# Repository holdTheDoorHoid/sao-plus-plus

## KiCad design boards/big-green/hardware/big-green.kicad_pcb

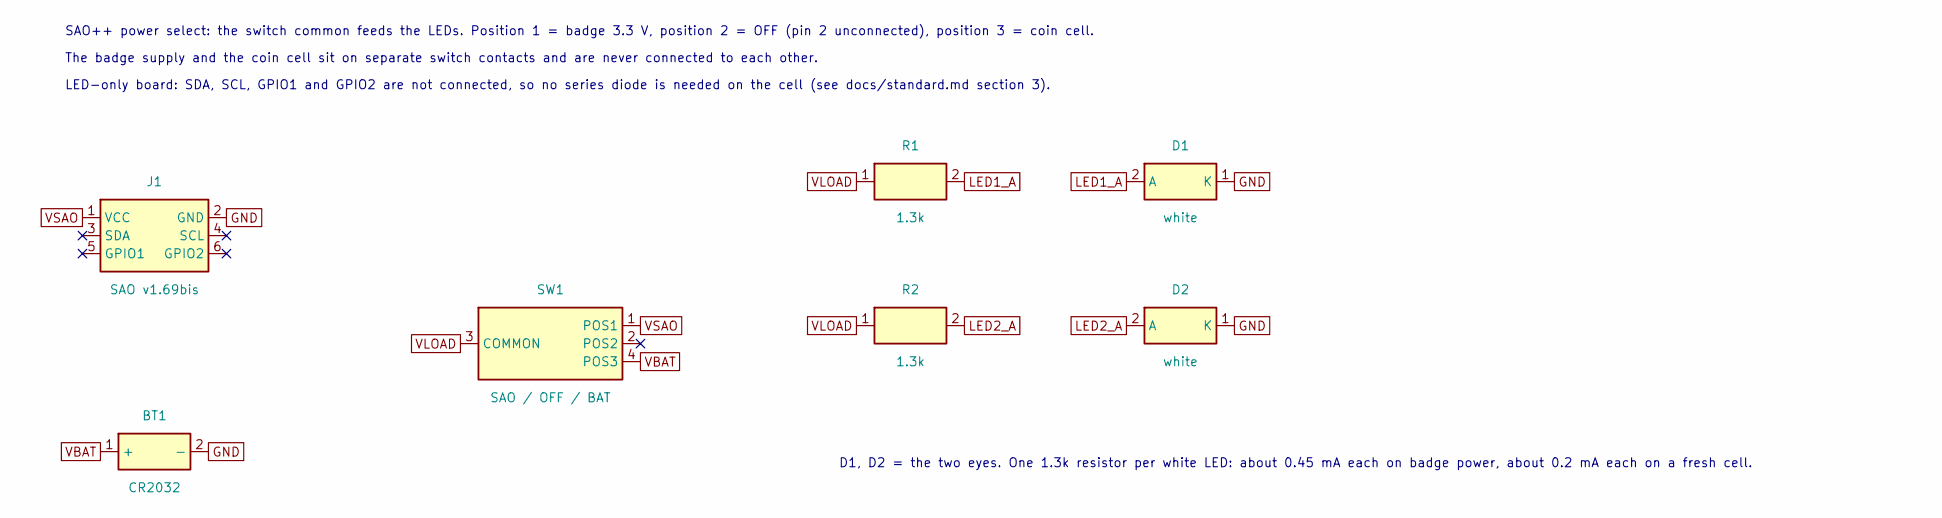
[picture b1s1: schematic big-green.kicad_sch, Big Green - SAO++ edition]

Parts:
BT1: CR2032; SAOPP_BAT-01_CR2032_SMD_TE_BAT-HLD-001; MPN BAT-HLD-001; LCSC C7501066
D1, D2: white; SAOPP_LED-10_1206_ReverseMount_ThroughBoard; MPN LTW-C230DS; LCSC C575513
J1: SAO v1.69bis; SAOPP_CONN-01_BoxHeader_2x03_P2.54mm_SMD_XFCN_BH254VS-6P; MPN BH254VS-6P; LCSC C492445
R1, R2: 1.3k; SAOPP_R_0603_1608Metric; MPN 0603WAF1301T5E; LCSC C22767
SW1: SAO / OFF / BAT; SAOPP_SW-01_Slide_SP3T_CK_PCM13SMTR; MPN PCM13SMTR; LCSC C221842

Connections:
GND: BT1.2 (-), D1.1 (K), D2.1 (K), J1.2 (GND)
LED1_A: D1.2 (A), R1.2
LED2_A: D2.2 (A), R2.2
VBAT: BT1.1 (+), SW1.4 (POS3)
VLOAD: R1.1, R2.1, SW1.3 (COMMON)
VSAO: J1.1 (VCC), SW1.1 (POS1)

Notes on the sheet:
SAO++ power select: the switch common feeds the LEDs. Position 1 = badge 3.3 V, position 2 = OFF (pin 2 unconnected), position 3 = coin cell.
The badge supply and the coin cell sit on separate switch contacts and are never connected to each other.
LED-only board: SDA, SCL, GPIO1 and GPIO2 are not connected, so no series diode is needed on the cell (see docs/standard.md section 3).
D1, D2 = the two eyes. One 1.3k resistor per white LED: about 0.45 mA each on badge power, about 0.2 mA each on a fresh cell.

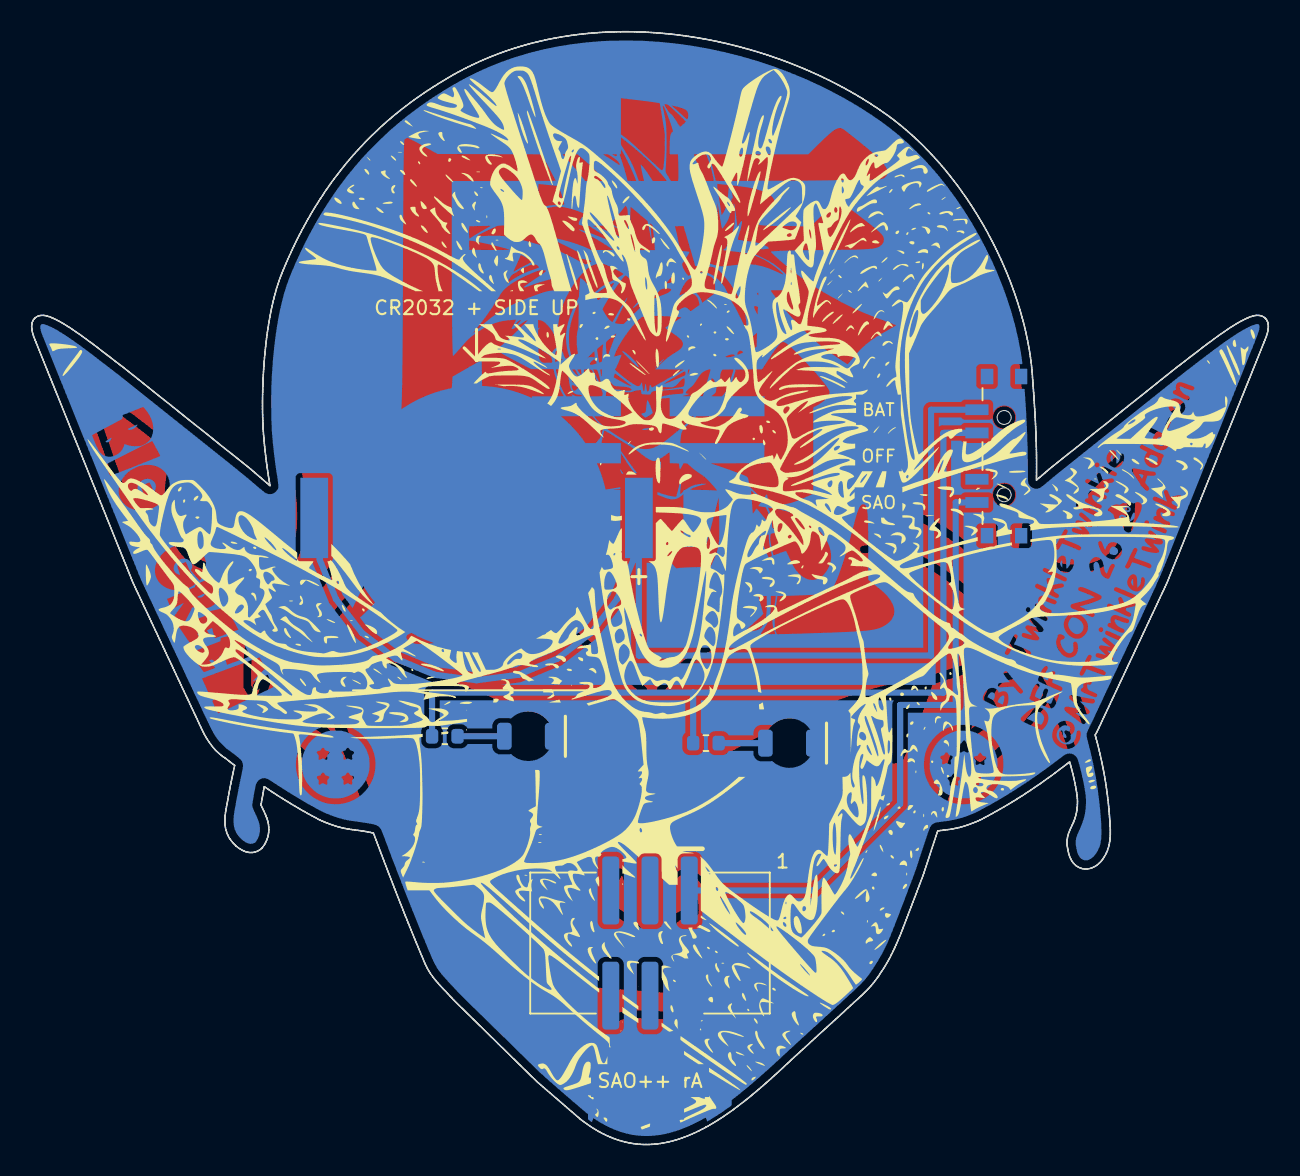
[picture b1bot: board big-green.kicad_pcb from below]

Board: 2 copper layers, 80.0 x 72.0 mm, 12 parts (7 on the bottom side), 6 nets.

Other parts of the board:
B.Cu: LOGO; B.Cu_g1620
B.Silk: LOGO; B.Silk_g1624
F.Cu: LOGO; F.Cu_g1626
F.Mask: LOGO; F.Mask_g1628
F.Silk: LOGO; F.Silk_g1630

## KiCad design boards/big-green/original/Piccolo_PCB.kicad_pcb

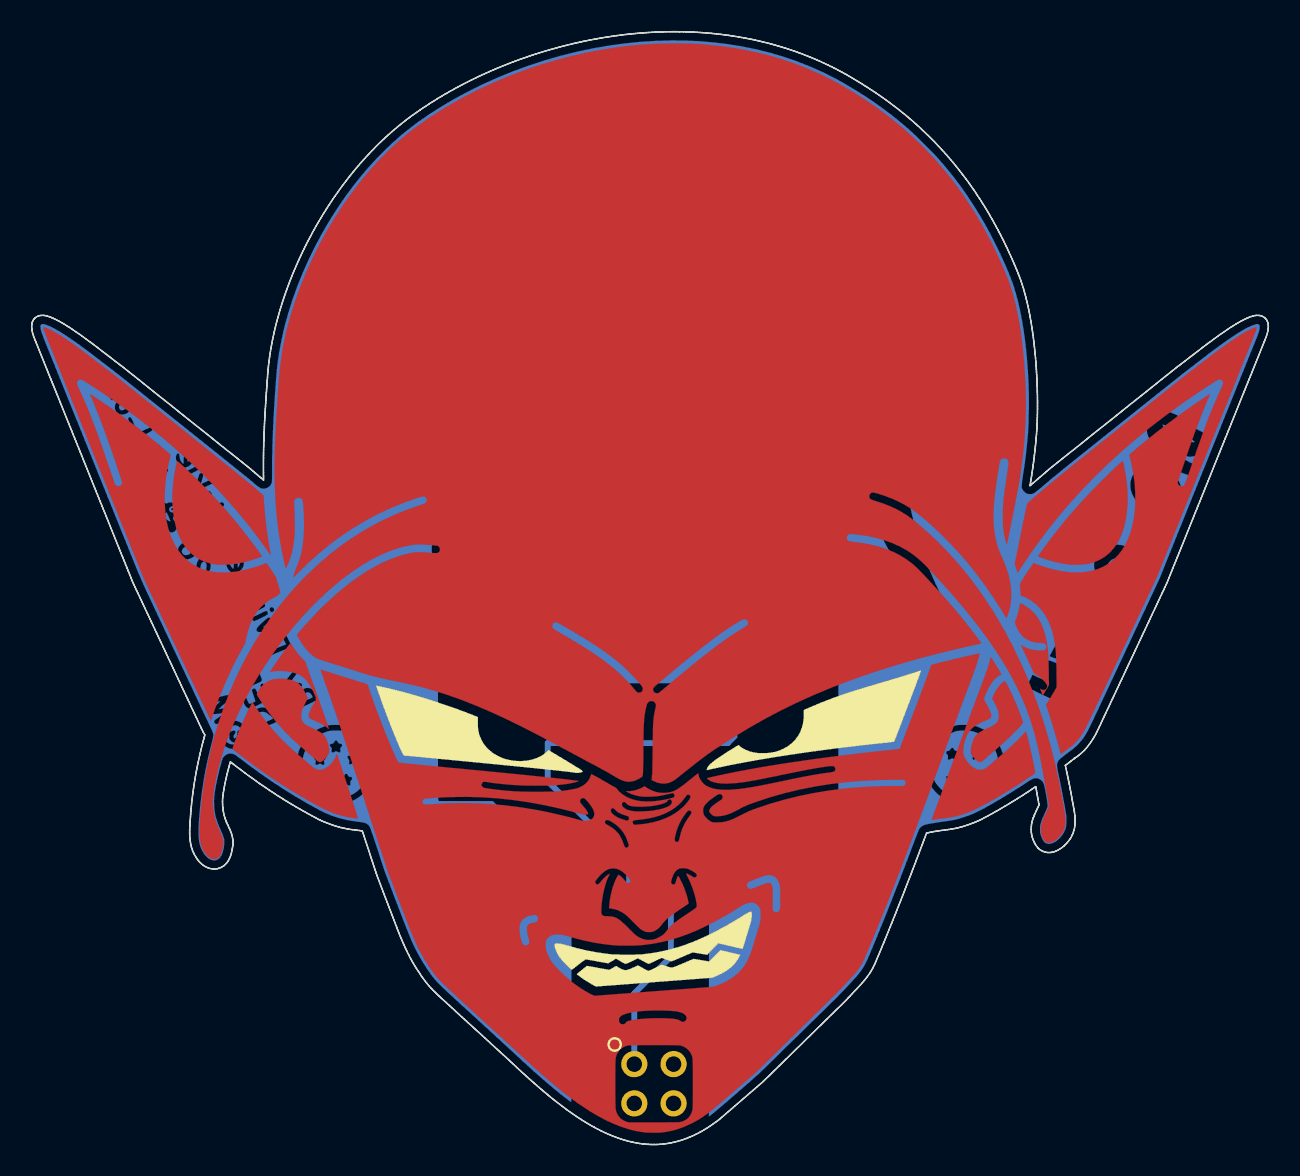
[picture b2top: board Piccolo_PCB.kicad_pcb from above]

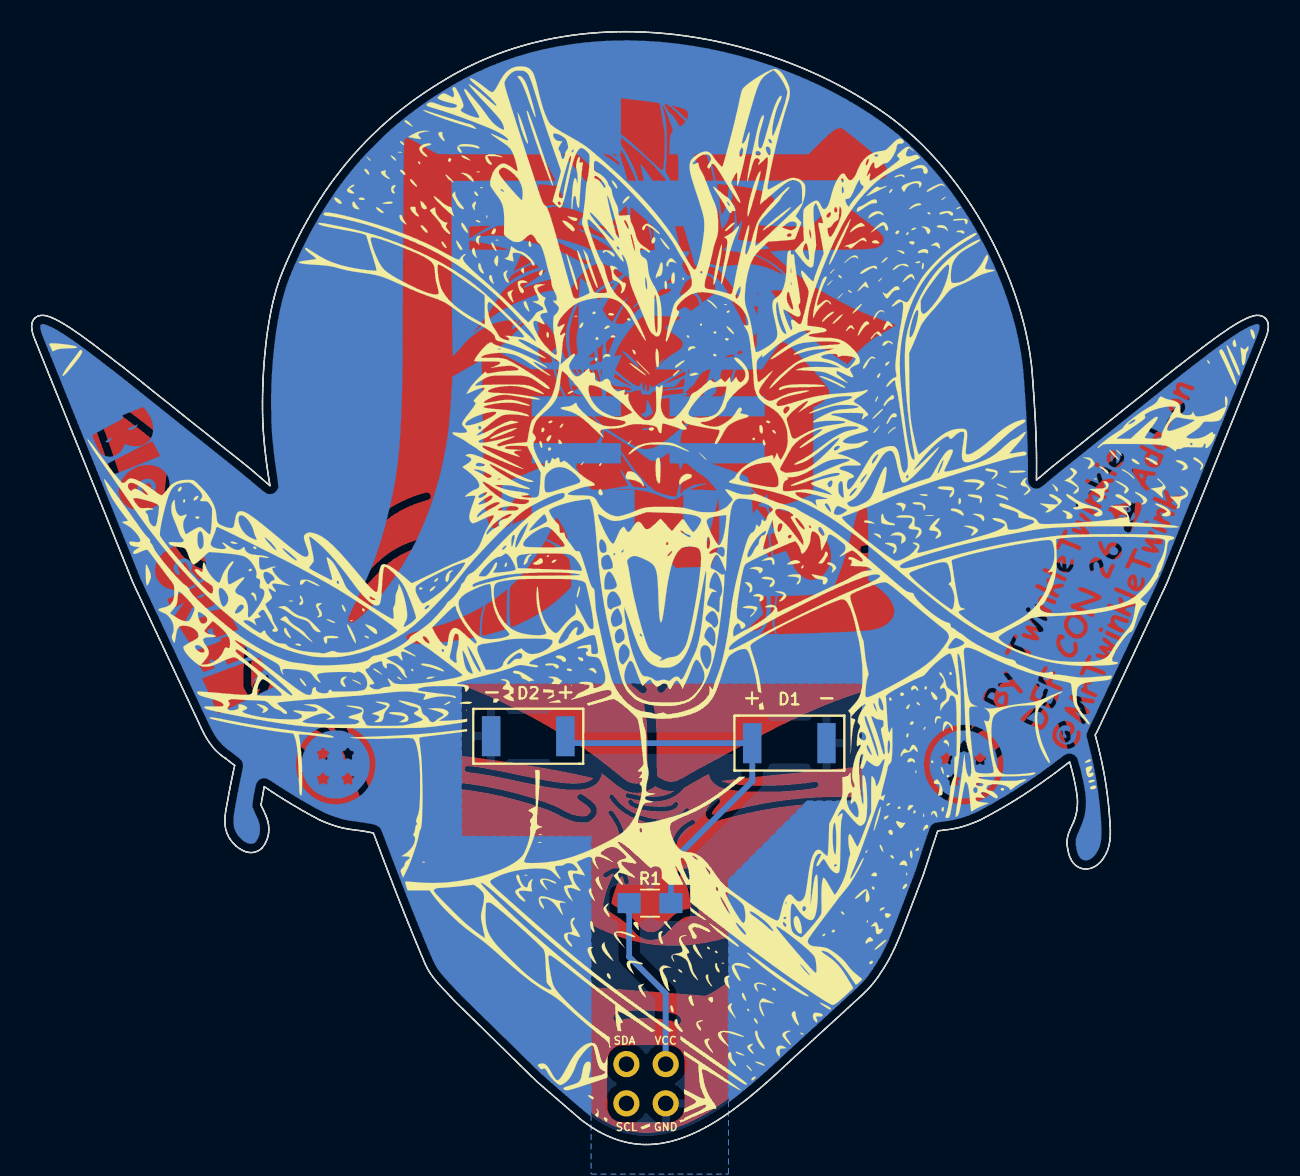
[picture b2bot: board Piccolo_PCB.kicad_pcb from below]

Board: 2 copper layers, 80.0 x 72.0 mm, 9 parts (3 on the bottom side), 3 nets.

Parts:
B.Cu: LOGO; B.Cu_g1620
B.Silk: LOGO; B.Silk_g1624
D1, D2: LED; LED_OSRAM_TOPLED_LxT776
F.Cu: LOGO; F.Cu_g1626
F.Mask: LOGO; F.Mask_g1628
F.Silk: LOGO; F.Silk_g1630
R1: R51; R_0805_HandSoldering
X1: Badgelife_shitty_connector; Badgelife-Shitty-2x2

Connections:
unnamed: D1.1, D2.1, X1.2
unnamed: D1.2, D2.2, R1.1
unnamed: R1.2, X1.1

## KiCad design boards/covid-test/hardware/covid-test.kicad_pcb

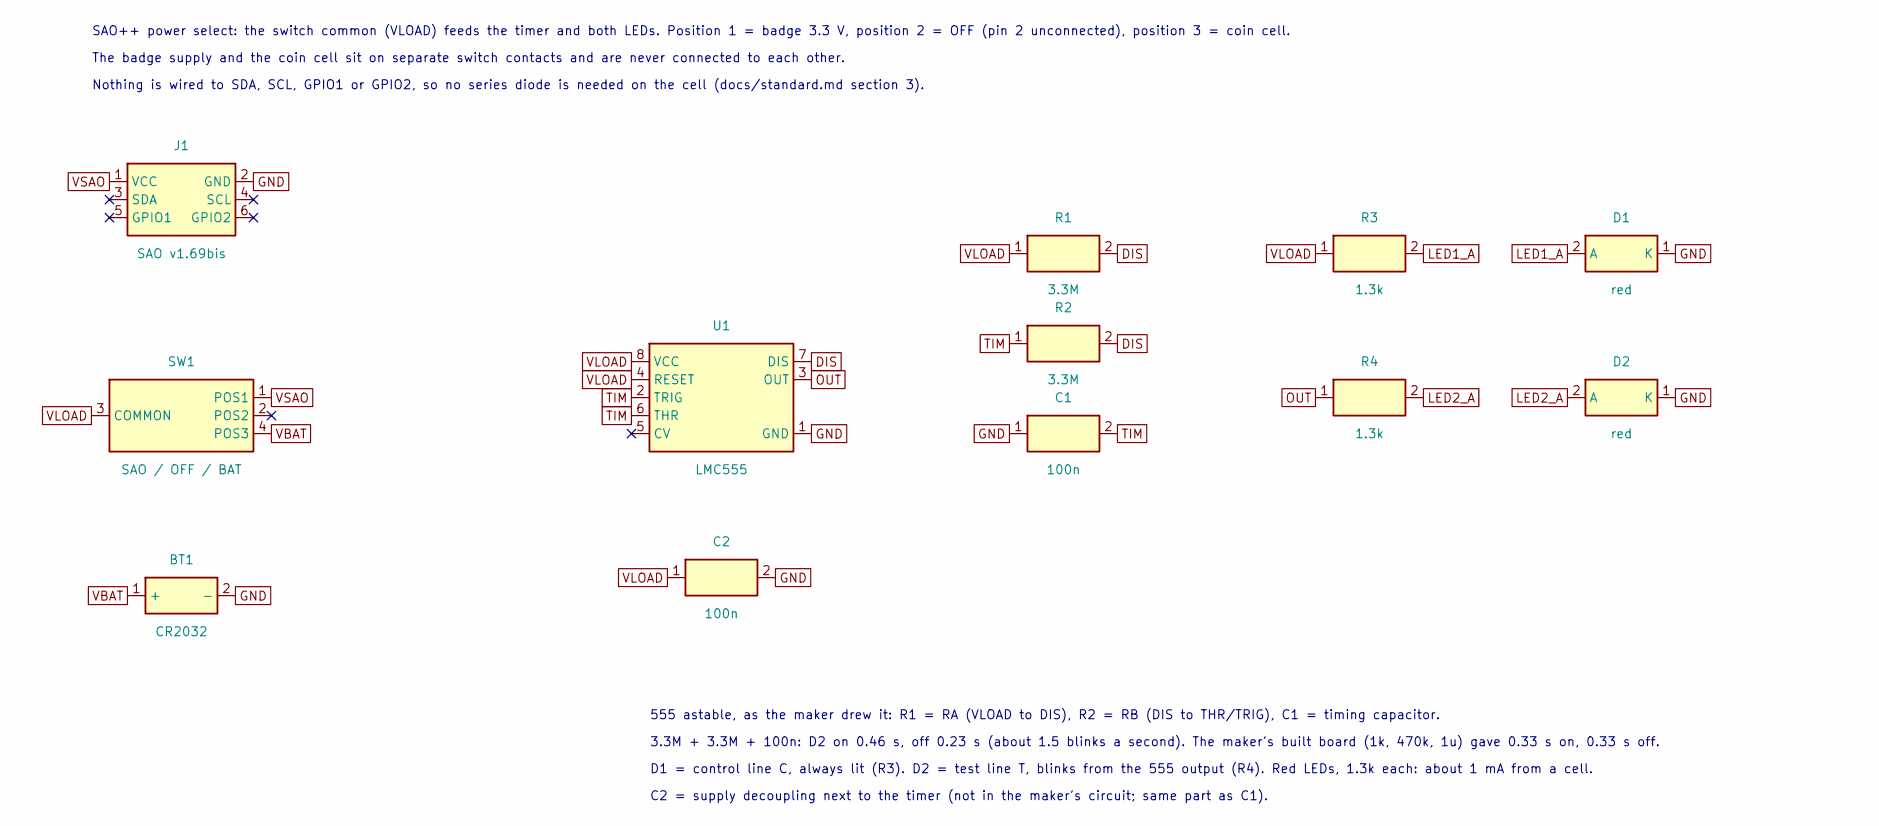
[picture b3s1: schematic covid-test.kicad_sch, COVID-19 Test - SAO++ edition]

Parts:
BT1: CR2032; SAOPP_BAT-01_CR2032_SMD_TE_BAT-HLD-001; MPN BAT-HLD-001; LCSC C7501066
C1, C2: 100n; SAOPP_C_0603_1608Metric; MPN CC0603KRX7R9BB104; LCSC C14663
D1, D2: red; SAOPP_LED-10_1206_ReverseMount_ThroughBoard; MPN LTST-C230KRKT; LCSC C125107
J1: SAO v1.69bis; SAOPP_CONN-01_BoxHeader_2x03_P2.54mm_SMD_XFCN_BH254VS-6P; MPN BH254VS-6P; LCSC C492445
R1, R2: 3.3M; R_0603_1608Metric; MPN 0603WAF3304T5E; LCSC C26096
R3, R4: 1.3k; SAOPP_R_0603_1608Metric; MPN 0603WAF1301T5E; LCSC C22767
SW1: SAO / OFF / BAT; SAOPP_SW-01_Slide_SP3T_CK_PCM13SMTR; MPN PCM13SMTR; LCSC C221842
U1: LMC555; SOIC-8_3.9x4.9mm_P1.27mm; MPN LMC555CMX/NOPB; LCSC C90760

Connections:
DIS: R1.2, R2.2, U1.7 (DIS)
GND: BT1.2 (-), C1.1, C2.2, D1.1 (K), D2.1 (K), J1.2 (GND), U1.1 (GND)
LED1_A: D1.2 (A), R3.2
LED2_A: D2.2 (A), R4.2
OUT: R4.1, U1.3 (OUT)
TIM: C1.2, R2.1, U1.2 (TRIG), U1.6 (THR)
VBAT: BT1.1 (+), SW1.4 (POS3)
VLOAD: C2.1, R1.1, R3.1, SW1.3 (COMMON), U1.4 (RESET), U1.8 (VCC)
VSAO: J1.1 (VCC), SW1.1 (POS1)

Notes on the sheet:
SAO++ power select: the switch common (VLOAD) feeds the timer and both LEDs. Position 1 = badge 3.3 V, position 2 = OFF (pin 2 unconnected), position 3 = coin cell.
The badge supply and the coin cell sit on separate switch contacts and are never connected to each other.
Nothing is wired to SDA, SCL, GPIO1 or GPIO2, so no series diode is needed on the cell (docs/standard.md section 3).
555 astable, as the maker drew it: R1 = RA (VLOAD to DIS), R2 = RB (DIS to THR/TRIG), C1 = timing capacitor.
3.3M + 3.3M + 100n: D2 on 0.46 s, off 0.23 s (about 1.5 blinks a second). The maker's built board (1k, 470k, 1u) gave 0.33 s on, 0.33 s off.
D1 = control line C, always lit (R3). D2 = test line T, blinks from the 555 output (R4). Red LEDs, 1.3k each: about 1 mA from a cell.
C2 = supply decoupling next to the timer (not in the maker's circuit; same part as C1).

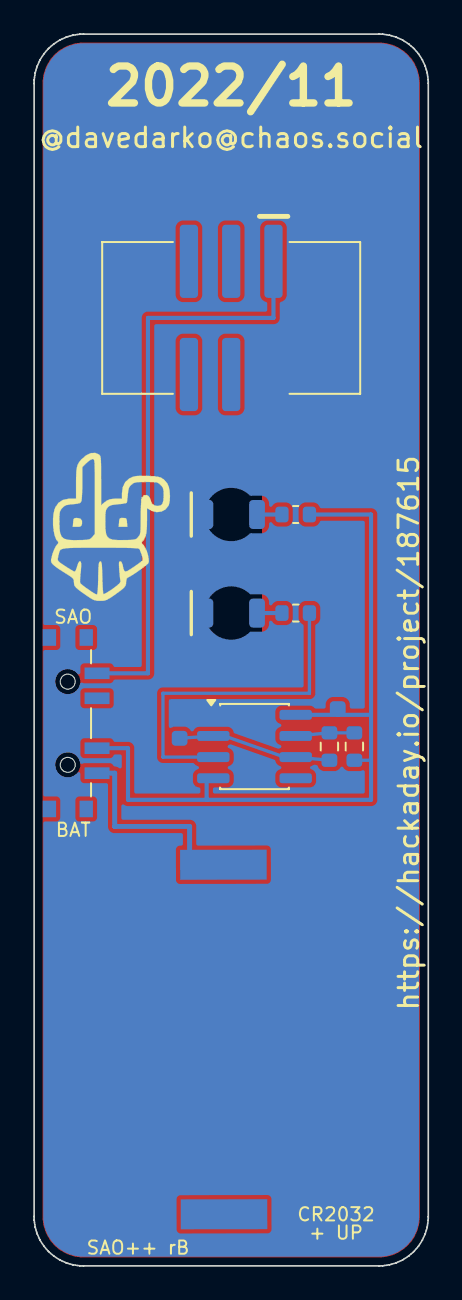
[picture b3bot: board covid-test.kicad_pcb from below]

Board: 2 copper layers, 23.7 x 74.0 mm, 14 parts (13 on the bottom side), 9 nets.

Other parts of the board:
Ref**: Val**; finalShadow
Ref**#2: Val**; davedarko_logo_silk_ext

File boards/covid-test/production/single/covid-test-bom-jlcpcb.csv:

Comment,Designator,Footprint,LCSC Part #
CR2032,BT1,SAOPP_BAT-01_CR2032_SMD_TE_BAT-HLD-001,C7501066
100n,"C1,C2",SAOPP_C_0603_1608Metric,C14663
red,"D1,D2",SAOPP_LED-10_1206_ReverseMount_ThroughBoard,C125107
SAO v1.69bis,J1,SAOPP_CONN-01_BoxHeader_2x03_P2.54mm_SMD_XFCN_BH254VS-6P,C492445
3.3M,"R1,R2",R_0603_1608Metric,C26096
1.3k,"R3,R4",SAOPP_R_0603_1608Metric,C22767
SAO / OFF / BAT,SW1,SAOPP_SW-01_Slide_SP3T_CK_PCM13SMTR,C221842
LMC555,U1,SOIC-8_3.9x4.9mm_P1.27mm,C90760

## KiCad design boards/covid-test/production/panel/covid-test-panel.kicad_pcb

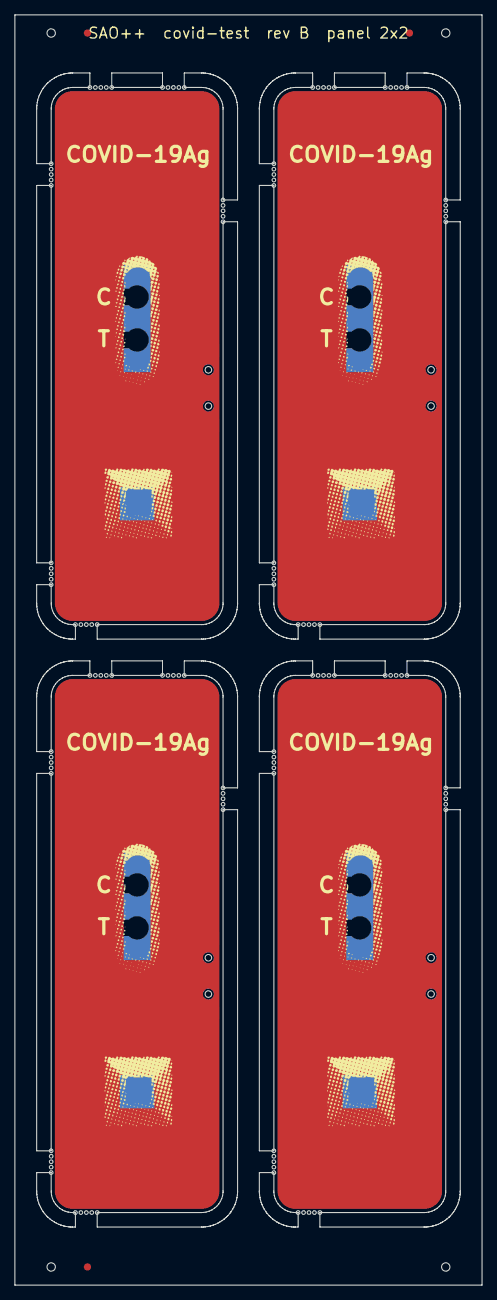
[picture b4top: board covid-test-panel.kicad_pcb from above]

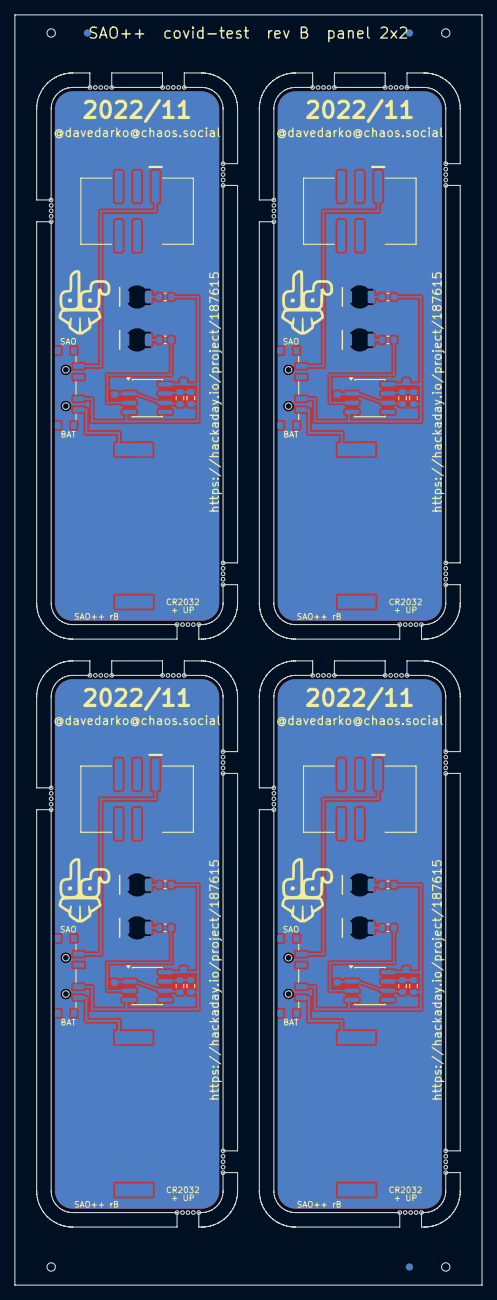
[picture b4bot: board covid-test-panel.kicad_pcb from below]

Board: 2 copper layers, 64.4 x 175.0 mm, 56 parts (52 on the bottom side), 36 nets.

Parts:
BT101, BT201, BT301, BT401: CR2032; SAOPP_BAT-01_CR2032_SMD_TE_BAT-HLD-001
C101, C102, C201, C202, C301, C302, C401, C402: 100n; SAOPP_C_0603_1608Metric
D101, D102, D201, D202, D301, D302, D401, D402: red; SAOPP_LED-10_1206_ReverseMount_ThroughBoard
J101, J201, J301, J401: SAO v1.69bis; SAOPP_CONN-01_BoxHeader_2x03_P2.54mm_SMD_XFCN_BH254VS-6P
R101, R102, R201, R202, R301, R302, R401, R402: 3.3M; R_0603_1608Metric
R103, R104, R203, R204, R303, R304, R403, R404: 1.3k; SAOPP_R_0603_1608Metric
Ref**: Val**; finalShadow
Ref**#2, Ref**#3, Ref**#4: Val**; finalShadow
Ref**#5, Ref**#6, Ref**#7, Ref**#8: Val**; davedarko_logo_silk_ext
SW101, SW201, SW301, SW401: SAO / OFF / BAT; SAOPP_SW-01_Slide_SP3T_CK_PCM13SMTR
U101, U201, U301, U401: LMC555; SOIC-8_3.9x4.9mm_P1.27mm

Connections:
B2-DIS: R201.2, R202.2, U201.7
B2-GND: BT201.2, C201.1, C202.2, D201.1, D202.1, J201.2, U201.1
B2-LED1_A: D201.2, R203.2
B2-LED2_A: D202.2, R204.2
B2-OUT: R204.1, U201.3
B2-TIM: C201.2, R202.1, U201.2, U201.6
B2-VBAT: BT201.1, SW201.4
B2-VLOAD: C202.1, R201.1, R203.1, SW201.3, U201.4, U201.8
B2-VSAO: J201.1, SW201.1
B3-DIS: R301.2, R302.2, U301.7
B3-GND: BT301.2, C301.1, C302.2, D301.1, D302.1, J301.2, U301.1
B3-LED1_A: D301.2, R303.2
B3-LED2_A: D302.2, R304.2
B3-OUT: R304.1, U301.3
B3-TIM: C301.2, R302.1, U301.2, U301.6
B3-VBAT: BT301.1, SW301.4
B3-VLOAD: C302.1, R301.1, R303.1, SW301.3, U301.4, U301.8
B3-VSAO: J301.1, SW301.1
B4-DIS: R401.2, R402.2, U401.7
B4-GND: BT401.2, C401.1, C402.2, D401.1, D402.1, J401.2, U401.1
B4-LED1_A: D401.2, R403.2
B4-LED2_A: D402.2, R404.2
B4-OUT: R404.1, U401.3
B4-TIM: C401.2, R402.1, U401.2, U401.6
B4-VBAT: BT401.1, SW401.4
B4-VLOAD: C402.1, R401.1, R403.1, SW401.3, U401.4, U401.8
B4-VSAO: J401.1, SW401.1
DIS: R101.2, R102.2, U101.7
GND: BT101.2, C101.1, C102.2, D101.1, D102.1, J101.2, U101.1
LED1_A: D101.2, R103.2
LED2_A: D102.2, R104.2
OUT: R104.1, U101.3
TIM: C101.2, R102.1, U101.2, U101.6
VBAT: BT101.1, SW101.4
VLOAD: C102.1, R101.1, R103.1, SW101.3, U101.4, U101.8
VSAO: J101.1, SW101.1

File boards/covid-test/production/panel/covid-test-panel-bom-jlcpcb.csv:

Comment,Designator,Footprint,LCSC Part #
CR2032,"BT101,BT201,BT301,BT401",SAOPP_BAT-01_CR2032_SMD_TE_BAT-HLD-001,C7501066
100n,"C101,C102,C201,C202,C301,C302,C401,C402",SAOPP_C_0603_1608Metric,C14663
red,"D101,D102,D201,D202,D301,D302,D401,D402",SAOPP_LED-10_1206_ReverseMount_ThroughBoard,C125107
SAO v1.69bis,"J101,J201,J301,J401",SAOPP_CONN-01_BoxHeader_2x03_P2.54mm_SMD_XFCN_BH254VS-6P,C492445
3.3M,"R101,R102,R201,R202,R301,R302,R401,R402",R_0603_1608Metric,C26096
1.3k,"R103,R104,R203,R204,R303,R304,R403,R404",SAOPP_R_0603_1608Metric,C22767
SAO / OFF / BAT,"SW101,SW201,SW301,SW401",SAOPP_SW-01_Slide_SP3T_CK_PCM13SMTR,C221842
LMC555,"U101,U201,U301,U401",SOIC-8_3.9x4.9mm_P1.27mm,C90760

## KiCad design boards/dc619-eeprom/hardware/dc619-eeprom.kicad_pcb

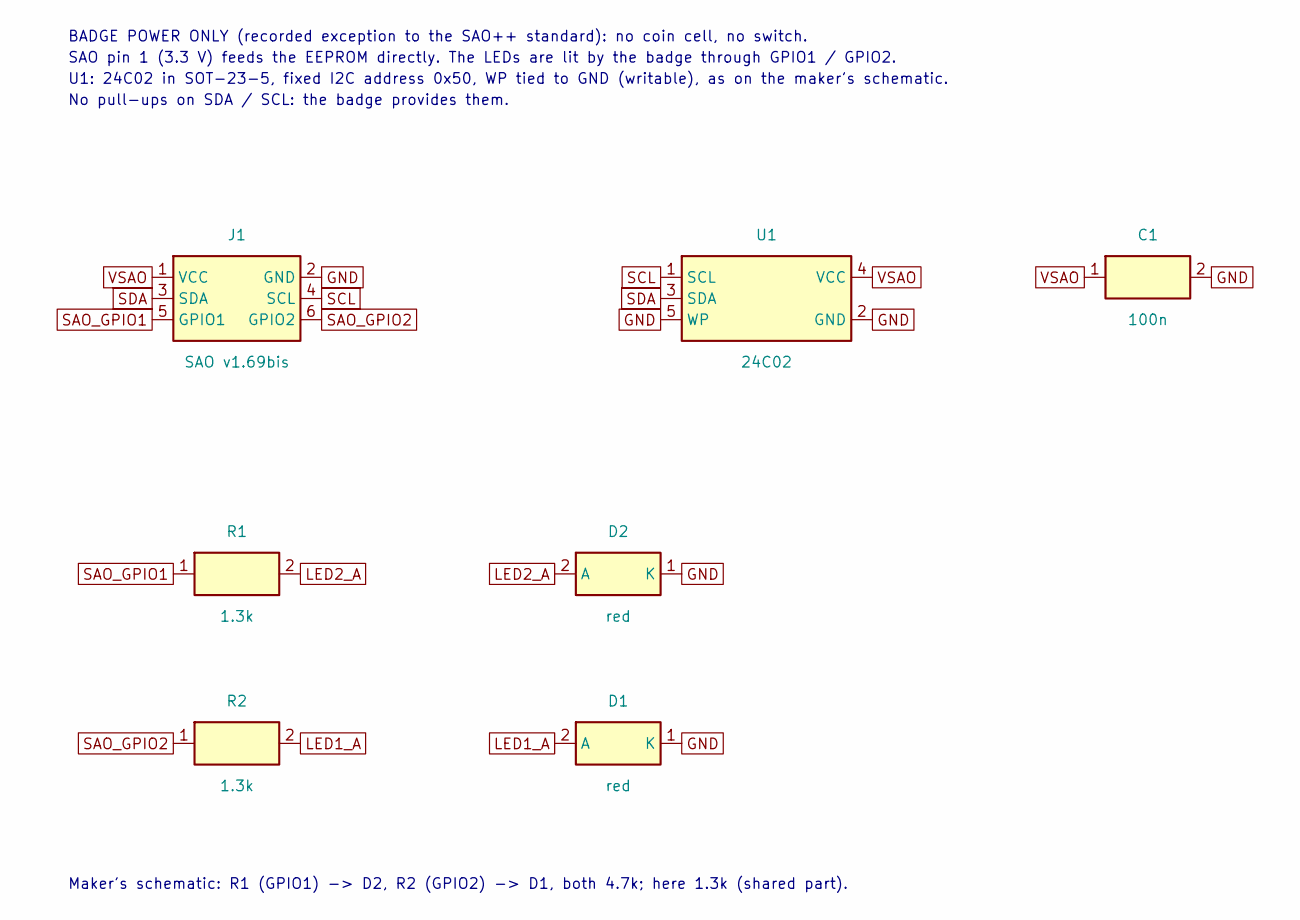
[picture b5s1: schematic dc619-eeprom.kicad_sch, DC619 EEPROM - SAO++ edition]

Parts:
C1: 100n; SAOPP_C_0603_1608Metric; MPN CC0603KRX7R9BB104; LCSC C14663
D1, D2: red; SAOPP_LED-10_1206_ReverseMount_ThroughBoard; MPN LTST-C230KRKT; LCSC C125107
J1: SAO v1.69bis; SAOPP_CONN-01_BoxHeader_2x03_P2.54mm_SMD_XFCN_BH254VS-6P; MPN BH254VS-6P; LCSC C492445
R1, R2: 1.3k; SAOPP_R_0603_1608Metric; MPN 0603WAF1301T5E; LCSC C22767
U1: 24C02; SOT-23-5; MPN AD24C02; LCSC C5125083

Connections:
GND: C1.2, D1.1 (K), D2.1 (K), J1.2 (GND), U1.2 (GND), U1.5 (WP)
LED1_A: D1.2 (A), R2.2
LED2_A: D2.2 (A), R1.2
SAO_GPIO1: J1.5 (GPIO1), R1.1
SAO_GPIO2: J1.6 (GPIO2), R2.1
SCL: J1.4 (SCL), U1.1 (SCL)
SDA: J1.3 (SDA), U1.3 (SDA)
VSAO: C1.1, J1.1 (VCC), U1.4 (VCC)

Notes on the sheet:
BADGE POWER ONLY (recorded exception to the SAO++ standard): no coin cell, no switch.
SAO pin 1 (3.3 V) feeds the EEPROM directly. The LEDs are lit by the badge through GPIO1 / GPIO2.
U1: 24C02 in SOT-23-5, fixed I2C address 0x50, WP tied to GND (writable), as on the maker's schematic.
No pull-ups on SDA / SCL: the badge provides them.
Maker's schematic: R1 (GPIO1) -> D2, R2 (GPIO2) -> D1, both 4.7k; here 1.3k (shared part).

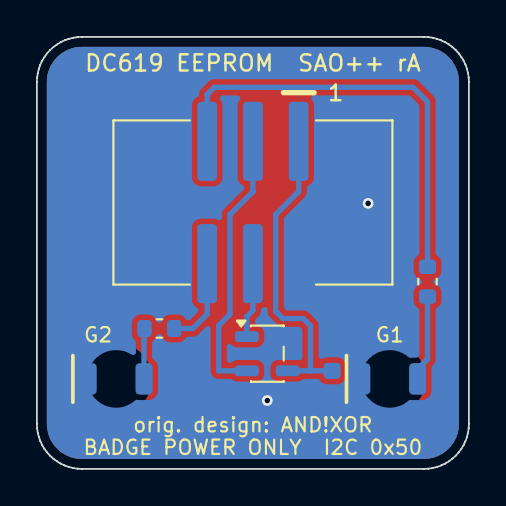
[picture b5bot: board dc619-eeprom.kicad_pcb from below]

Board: 2 copper layers, 24.0 x 24.0 mm, 7 parts (7 on the bottom side), 8 nets.

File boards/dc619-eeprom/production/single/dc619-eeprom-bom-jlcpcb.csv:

Comment,Designator,Footprint,LCSC Part #
100n,C1,SAOPP_C_0603_1608Metric,C14663
red,"D1,D2",SAOPP_LED-10_1206_ReverseMount_ThroughBoard,C125107
SAO v1.69bis,J1,SAOPP_CONN-01_BoxHeader_2x03_P2.54mm_SMD_XFCN_BH254VS-6P,C492445
1.3k,"R1,R2",SAOPP_R_0603_1608Metric,C22767
24C02,U1,SOT-23-5,C5125083

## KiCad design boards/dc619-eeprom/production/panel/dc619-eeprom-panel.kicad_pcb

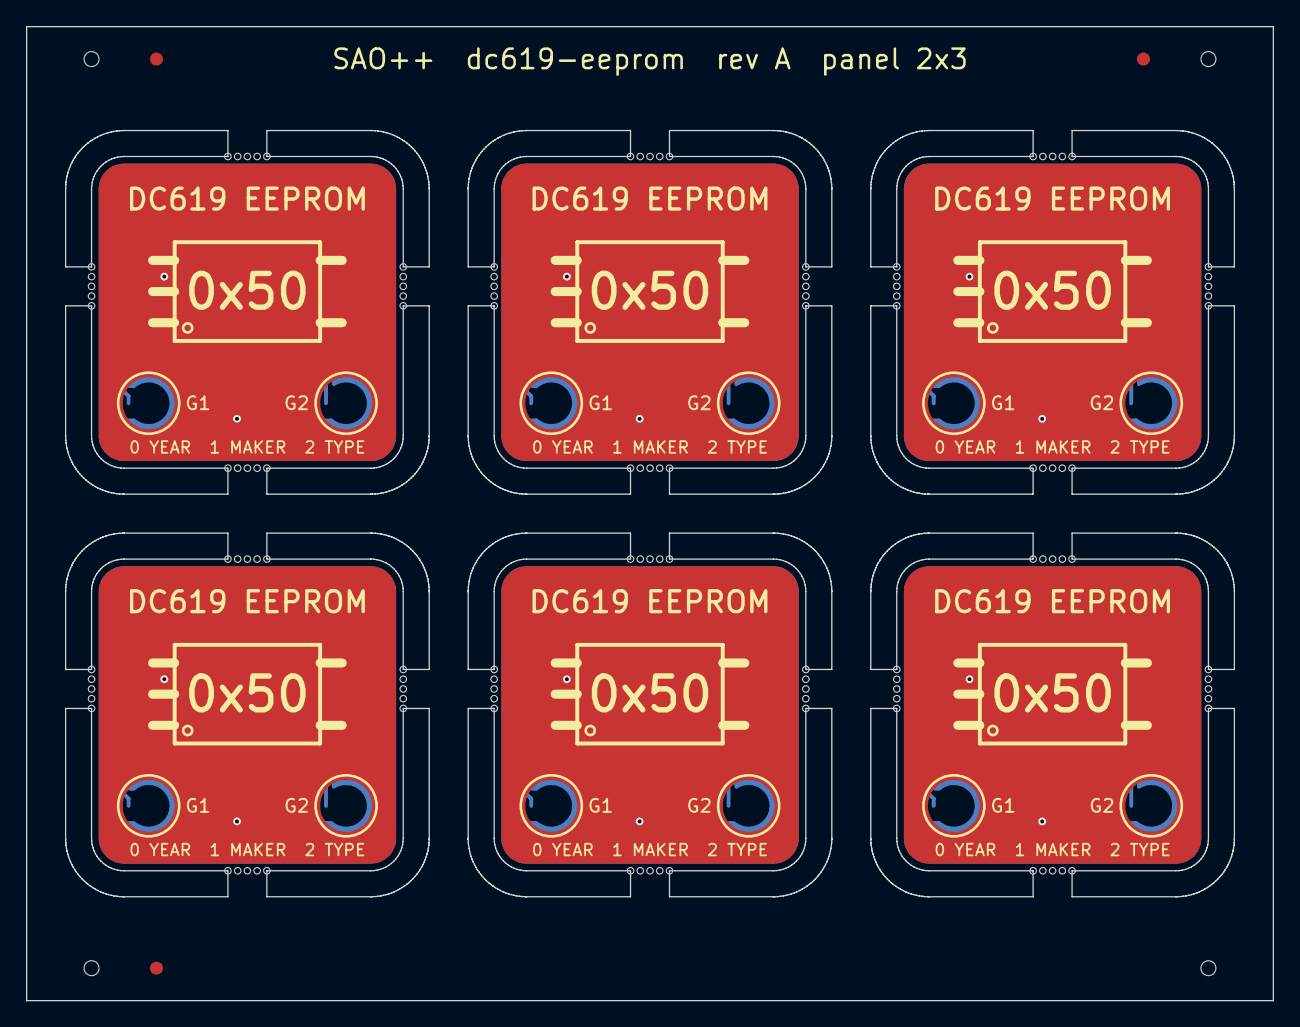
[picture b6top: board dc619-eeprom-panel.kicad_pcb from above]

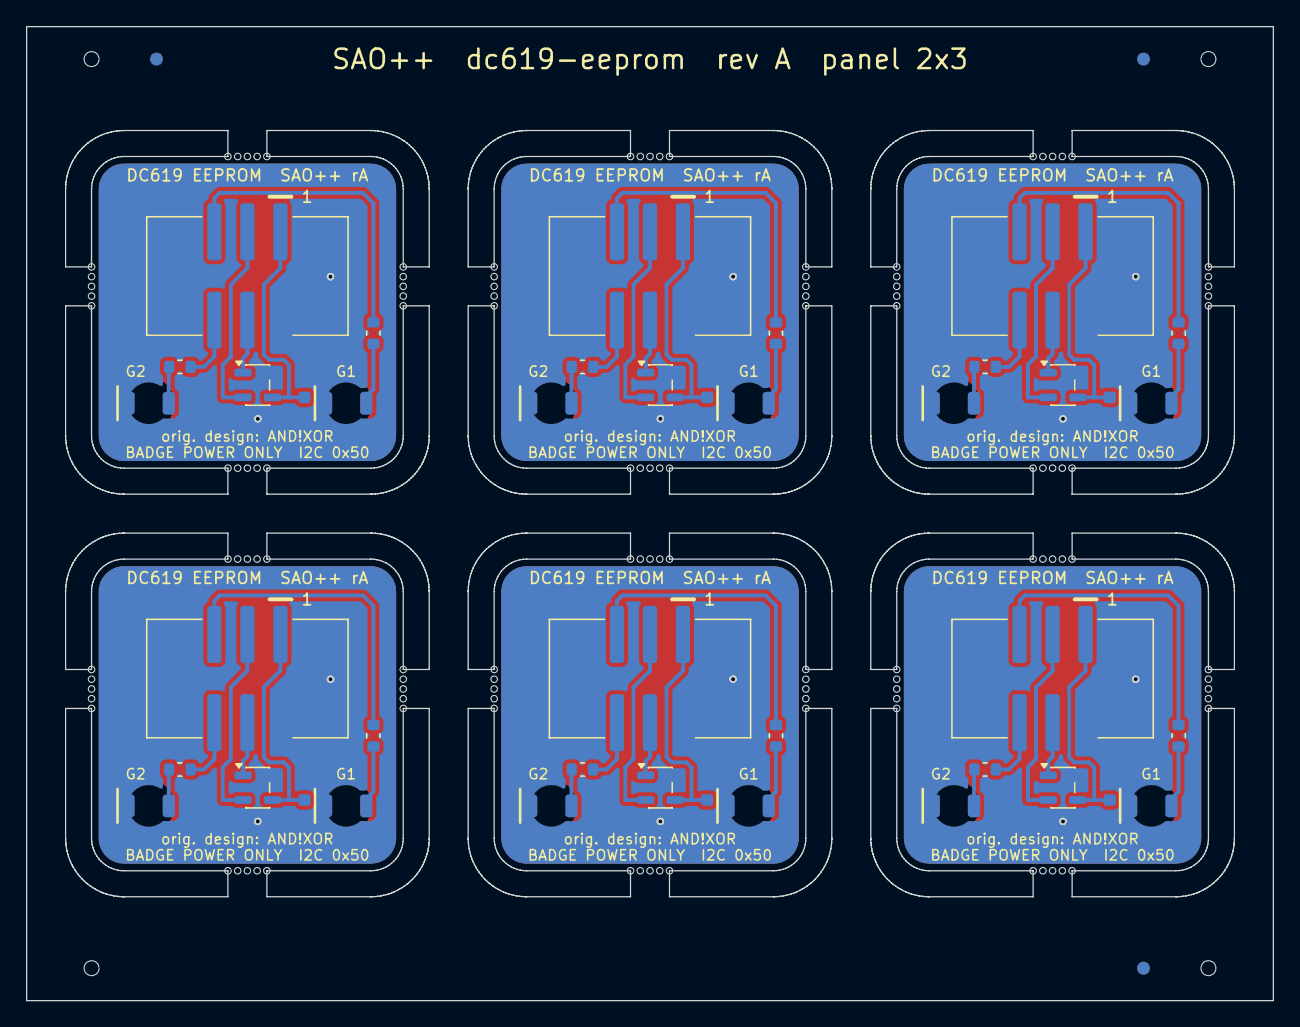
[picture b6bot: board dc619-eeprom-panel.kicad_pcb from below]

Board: 2 copper layers, 96.0 x 75.0 mm, 42 parts (42 on the bottom side), 48 nets.

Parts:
C101, C201, C301, C401, C501, C601: 100n; SAOPP_C_0603_1608Metric
D101, D102, D201, D202, D301, D302, D401, D402, D501, D502, D601, D602: red; SAOPP_LED-10_1206_ReverseMount_ThroughBoard
J101, J201, J301, J401, J501, J601: SAO v1.69bis; SAOPP_CONN-01_BoxHeader_2x03_P2.54mm_SMD_XFCN_BH254VS-6P
R101, R102, R201, R202, R301, R302, R401, R402, R501, R502, R601, R602: 1.3k; SAOPP_R_0603_1608Metric
U101, U201, U301, U401, U501, U601: 24C02; SOT-23-5

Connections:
B2-GND: C201.2, D201.1, D202.1, J201.2, U201.2, U201.5
B2-LED1_A: D201.2, R202.2
B2-LED2_A: D202.2, R201.2
B2-SAO_GPIO1: J201.5, R201.1
B2-SAO_GPIO2: J201.6, R202.1
B2-SCL: J201.4, U201.1
B2-SDA: J201.3, U201.3
B2-VSAO: C201.1, J201.1, U201.4
B3-GND: C301.2, D301.1, D302.1, J301.2, U301.2, U301.5
B3-LED1_A: D301.2, R302.2
B3-LED2_A: D302.2, R301.2
B3-SAO_GPIO1: J301.5, R301.1
B3-SAO_GPIO2: J301.6, R302.1
B3-SCL: J301.4, U301.1
B3-SDA: J301.3, U301.3
B3-VSAO: C301.1, J301.1, U301.4
B4-GND: C401.2, D401.1, D402.1, J401.2, U401.2, U401.5
B4-LED1_A: D401.2, R402.2
B4-LED2_A: D402.2, R401.2
B4-SAO_GPIO1: J401.5, R401.1
B4-SAO_GPIO2: J401.6, R402.1
B4-SCL: J401.4, U401.1
B4-SDA: J401.3, U401.3
B4-VSAO: C401.1, J401.1, U401.4
B5-GND: C501.2, D501.1, D502.1, J501.2, U501.2, U501.5
B5-LED1_A: D501.2, R502.2
B5-LED2_A: D502.2, R501.2
B5-SAO_GPIO1: J501.5, R501.1
B5-SAO_GPIO2: J501.6, R502.1
B5-SCL: J501.4, U501.1
B5-SDA: J501.3, U501.3
B5-VSAO: C501.1, J501.1, U501.4
B6-GND: C601.2, D601.1, D602.1, J601.2, U601.2, U601.5
B6-LED1_A: D601.2, R602.2
B6-LED2_A: D602.2, R601.2
B6-SAO_GPIO1: J601.5, R601.1
B6-SAO_GPIO2: J601.6, R602.1
B6-SCL: J601.4, U601.1
B6-SDA: J601.3, U601.3
B6-VSAO: C601.1, J601.1, U601.4
GND: C101.2, D101.1, D102.1, J101.2, U101.2, U101.5
LED1_A: D101.2, R102.2
LED2_A: D102.2, R101.2
SAO_GPIO1: J101.5, R101.1
SAO_GPIO2: J101.6, R102.1
SCL: J101.4, U101.1
SDA: J101.3, U101.3
VSAO: C101.1, J101.1, U101.4

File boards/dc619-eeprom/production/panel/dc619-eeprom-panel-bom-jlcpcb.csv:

Comment,Designator,Footprint,LCSC Part #
100n,"C101,C201,C301,C401,C501,C601",SAOPP_C_0603_1608Metric,C14663
red,"D101,D102,D201,D202,D301,D302,D401,D402,D501,D502,D601,D602",SAOPP_LED-10_1206_ReverseMount_ThroughBoard,C125107
SAO v1.69bis,"J101,J201,J301,J401,J501,J601",SAOPP_CONN-01_BoxHeader_2x03_P2.54mm_SMD_XFCN_BH254VS-6P,C492445
1.3k,"R101,R102,R201,R202,R301,R302,R401,R402,R501,R502,R601,R602",SAOPP_R_0603_1608Metric,C22767
24C02,"U101,U201,U301,U401,U501,U601",SOT-23-5,C5125083
